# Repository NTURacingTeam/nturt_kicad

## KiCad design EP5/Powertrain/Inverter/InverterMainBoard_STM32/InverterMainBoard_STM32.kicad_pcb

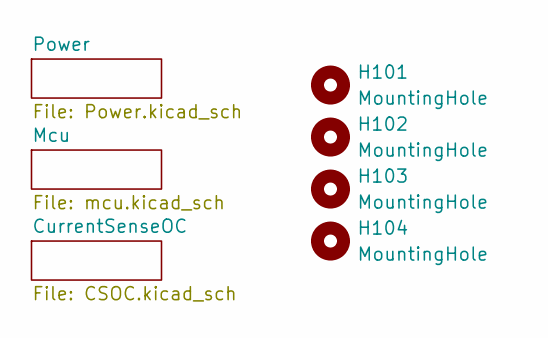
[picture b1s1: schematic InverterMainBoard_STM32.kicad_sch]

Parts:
H101, H102, H103, H104: MountingHole; MountingHole_4mm

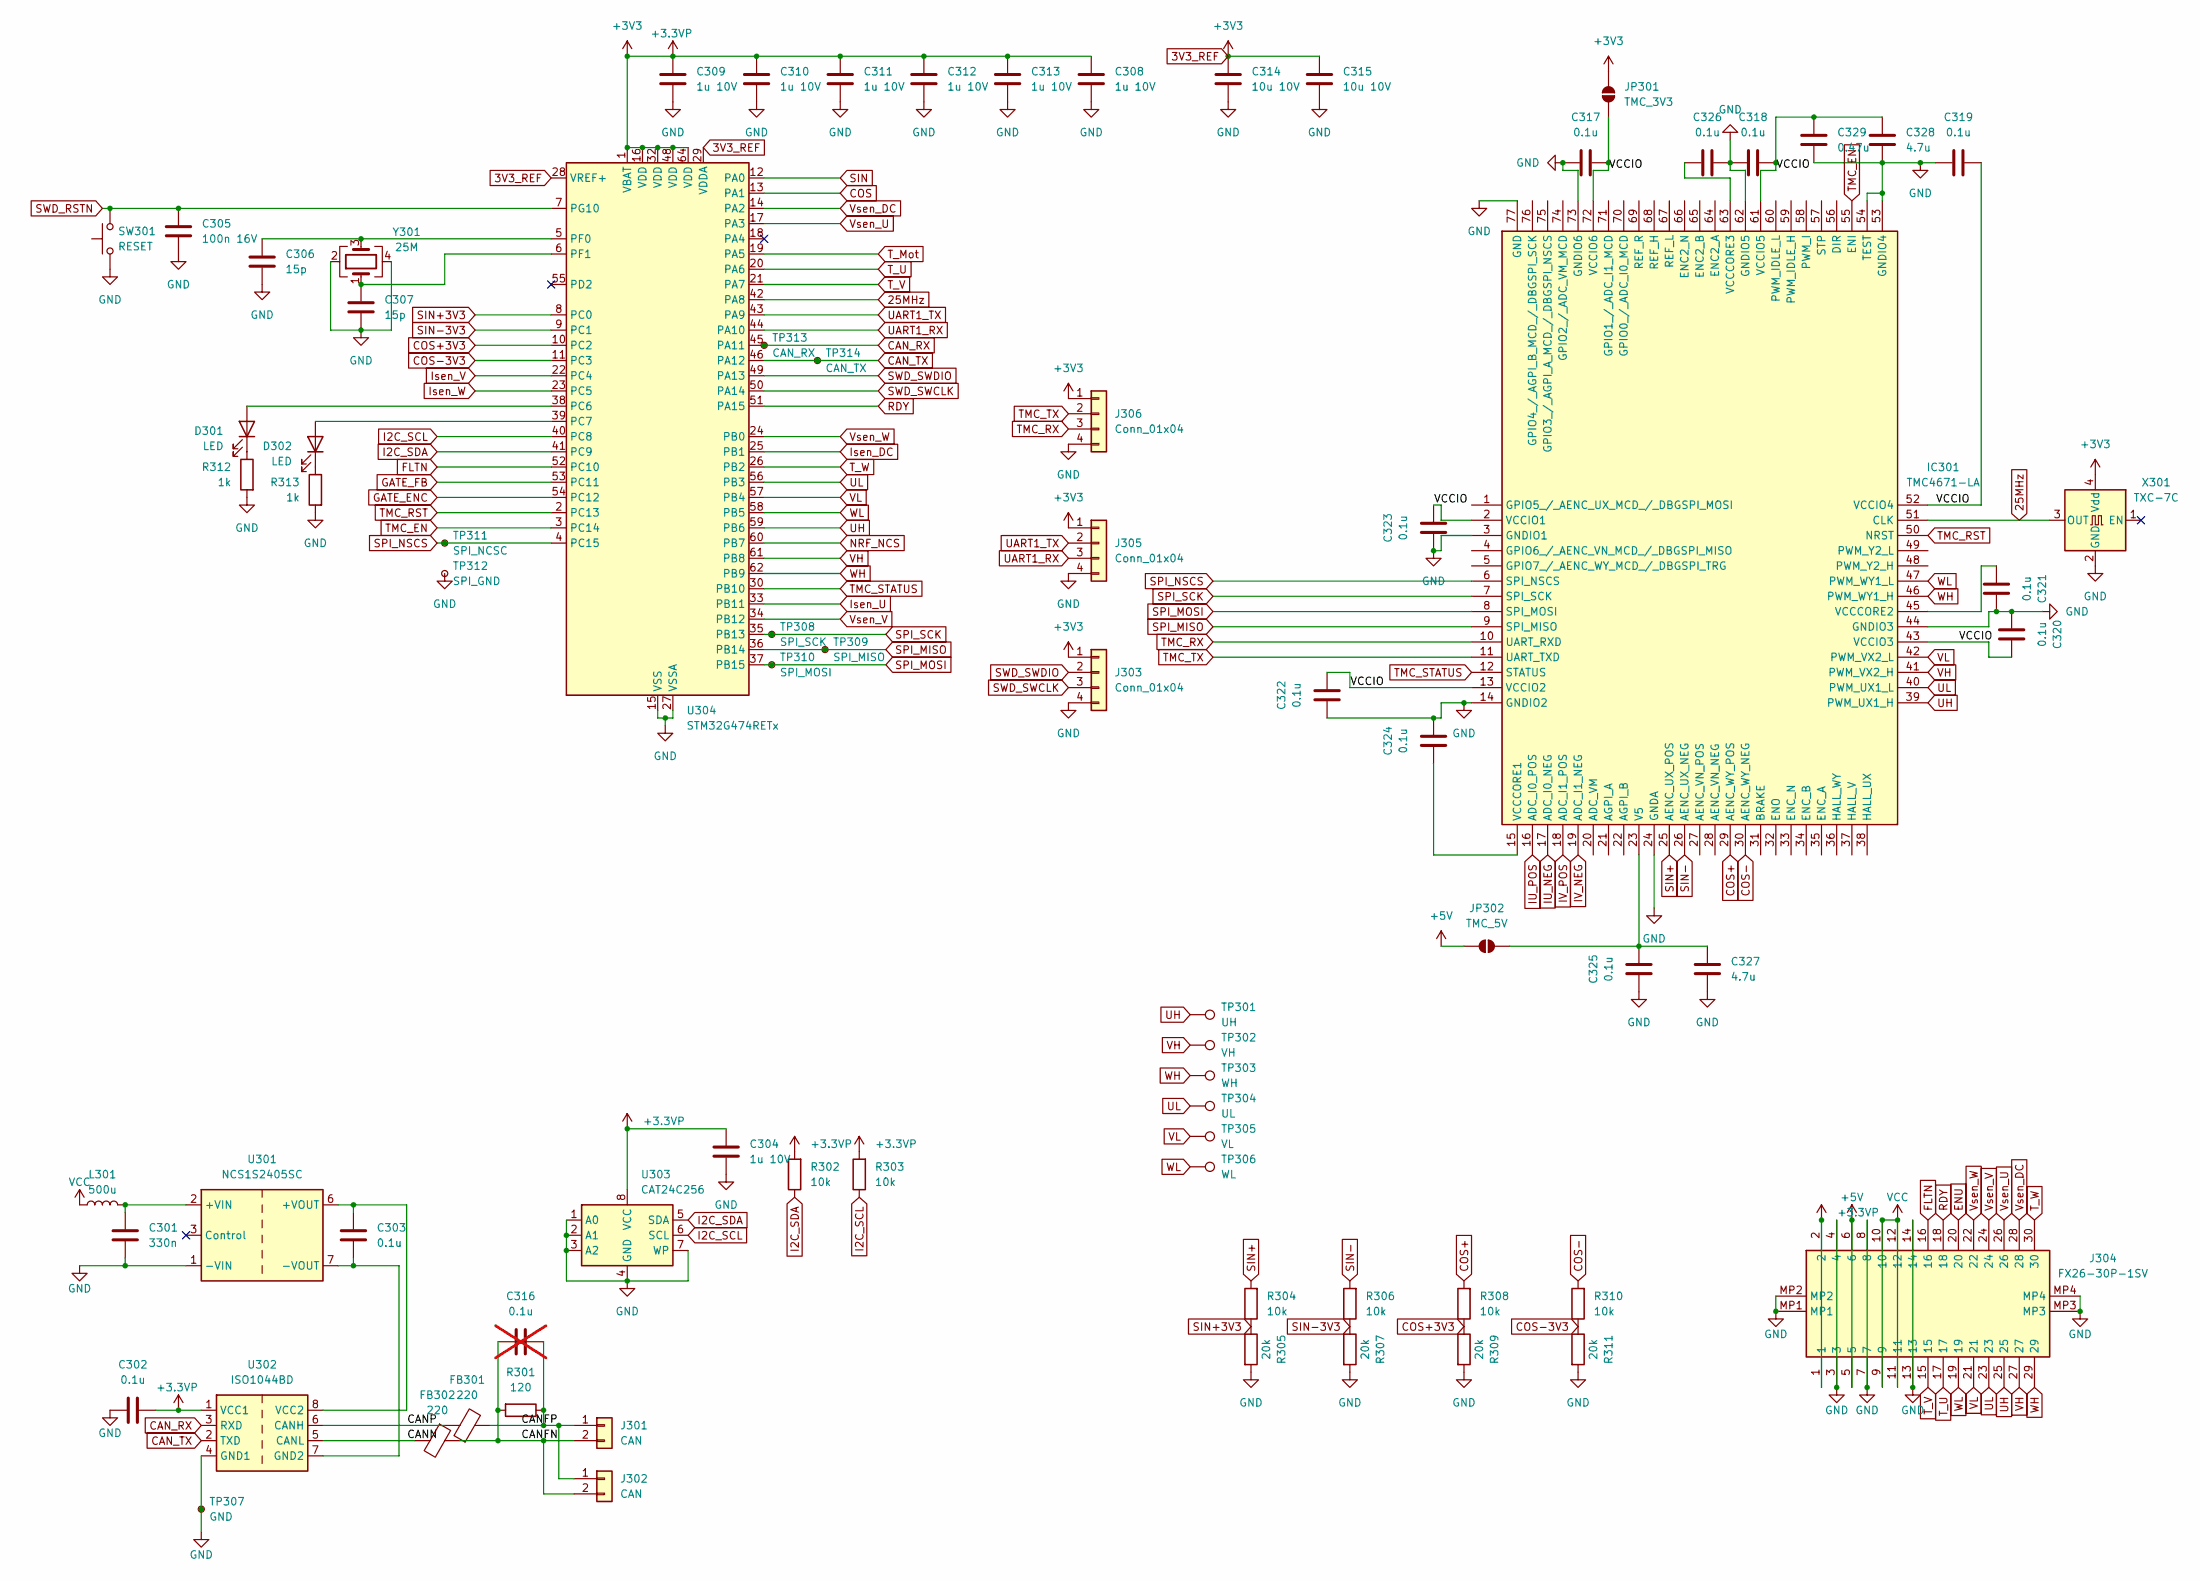
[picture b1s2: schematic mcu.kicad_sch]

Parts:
C301: 330n; C_0603_1608Metric
C302, C303, C317, C318, C319, C320, C321, C322, C323, C324, C325, C326: 0.1u; C_0603_1608Metric
C304, C308, C309, C310, C311, C312, C313: 1u 10V; C_0603_1608Metric
C305: 100n 16V; C_0603_1608Metric
C306, C307: 15p; C_0603_1608Metric
C314, C315: 10u 10V; C_0603_1608Metric
C316: 0.1u; C_0603_1608Metric; not fitted
C327, C328: 4.7u; C_0603_1608Metric
C329: 0.47u; C_0603_1608Metric
D301, D302: LED; LED_0603_1608Metric
FB301, FB302: 220; R_0603_1608Metric
IC301: TMC4671-LA; QFN40P1050X650X90-77N; Mouser Part Number 700-TMC4671-LA
J301, J302: CAN; JST_XH_B2B-XH-A_1x02_P2.50mm_Vertical
J303, J305, J306: Conn_01x04; PinHeader_1x04_P2.54mm_Vertical
J304: FX26-30P-1SV; FX2630P1SV; Mouser Part Number 798-FX2630P1SV
JP301: TMC_3V3; SolderJumper-2_P1.3mm_Open_Pad1.0x1.5mm
JP302: TMC_5V; SolderJumper-2_P1.3mm_Open_Pad1.0x1.5mm
L301: 500u; L_Changjiang_FNR4030S
R301: 120; R_0603_1608Metric
R302, R303, R304, R306, R308, R310: 10k; R_0603_1608Metric
R305, R307, R309, R311: 20k; R_0603_1608Metric
R312, R313: 1k; R_0603_1608Metric
SW301: RESET; SW_Push_1P1T_XKB_TS-1187A
TP301: UH; TestPoint_Pad_D1.0mm
TP302: VH; TestPoint_Pad_D1.0mm
TP303: WH; TestPoint_Pad_D1.0mm
TP304: UL; TestPoint_Pad_D1.0mm
TP305: VL; TestPoint_Pad_D1.0mm
TP306: WL; TestPoint_Pad_D1.0mm
TP307: GND; TestPoint_Loop_D1.80mm_Drill1.0mm_Beaded
TP308: SPI_SCK; TestPoint_Pad_D1.0mm
TP309: SPI_MISO; TestPoint_Pad_D1.0mm
TP310: SPI_MOSI; TestPoint_Pad_D1.0mm
TP311: SPI_NCSC; TestPoint_Pad_D1.0mm
TP312: SPI_GND; TestPoint_Pad_D1.0mm
TP313: CAN_RX; TestPoint_Pad_D1.0mm
TP314: CAN_TX; TestPoint_Pad_D1.0mm
U301: NCS1S2405SC; Converter_DCDC_Murata_NCS1SxxxxSC_THT
U302: ISO1044BD; SOIC-8_3.9x4.9mm_P1.27mm
U303: CAT24C256; SOIC-8_3.9x4.9mm_P1.27mm
U304: STM32G474RETx; LQFP-64_10x10mm_P0.5mm
X301: TXC-7C; Oscillator_SMD_TXC_7C-4Pin_5.0x3.2mm
Y301: 25M; Crystal_SMD_3225-4Pin_3.2x2.5mm

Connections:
3V3_REF: C302.2, C304.1, C308.1, C309.1, C310.1, C311.1, C312.1, C313.1, C314.1, C315.1, J303.1, J304.1, J304.2, J305.1, J306.1, JP301.2 (B), R302.2, R303.2, U302.1 (VCC1), U303.8 (VCC), U304.1 (VBAT), U304.16 (VDD), U304.28 (VREF+), U304.29 (VDDA), U304.32 (VDD), U304.48 (VDD), U304.64 (VDD), X301.4 (Vdd); also elsewhere on the board
25MHz: IC301.51 (CLK), U304.42 (PA8), X301.3 (OUT)
+5V: J304.5, J304.6, JP302.2 (B); also elsewhere on the board
/Mcu/CANFN: C316.1, FB302.1, J301.2, J302.2, R301.2
/Mcu/CANFP: C316.2, FB301.2, J301.1, J302.1, R301.1
/Mcu/CANN: FB302.2, U302.5 (CANL)
/Mcu/CANP: FB301.1, U302.6 (CANH)
/Mcu/VCCIO: C317.2, C318.2, C319.2, C320.2, C322.2, C323.2, C328.2, C329.2, IC301.2 (VCCIO1), IC301.13 (VCCIO2), IC301.43 (VCCIO3), IC301.52 (VCCIO4), IC301.61 (VCCIO5), IC301.72 (VCCIO6), JP301.1 (A)
CAN_RX: TP313.1, U302.3 (RXD), U304.45 (PA11)
CAN_TX: TP314.1, U302.2 (TXD), U304.46 (PA12)
COS: U304.13 (PA1); also elsewhere on the board
COS+: IC301.29 (AENC_WY_POS), R308.2; also elsewhere on the board
COS+3V3: R308.1, R309.1, U304.10 (PC2)
COS-: IC301.30 (AENC_WY_NEG), R310.2; also elsewhere on the board
COS-3V3: R310.1, R311.1, U304.11 (PC3)
ENU: J304.20, U304.53 (PC11); also elsewhere on the board
FLTN: J304.16, U304.52 (PC10)
GATE_ENC: U304.54 (PC12); also elsewhere on the board
GND: C301.2, C302.1, C304.2, C305.1, C306.1, C307.1, C308.2, C309.2, C310.2, C311.2, C312.2, C313.2, C314.2, C315.2, C317.1, C318.1, C319.1, C320.1, C321.2, C322.1, C323.1, C324.2, C325.1, C326.2, C327.1, C328.1, C329.1, IC301.3 (GNDIO1), IC301.14 (GNDIO2), IC301.24 (GNDA), IC301.44 (GNDIO3), IC301.53 (GNDIO4), IC301.54 (TEST), IC301.62 (GNDIO5), IC301.73 (GNDIO6), IC301.77 (GND), J303.4, J304.3, J304.4, J304.7, J304.8, J304.13, J304.14, J304.MP1, J304.MP2, J304.MP3, J304.MP4, J305.4, J306.4, R305.2, R307.2, R309.2, R311.2, R312.2, R313.2, SW301.1, TP307.1, TP312.1, U301.1 (-VIN), U302.4 (GND1), U303.1 (A0), U303.2 (A1), U303.3 (A2), U303.4 (GND), U303.7 (WP), U304.15 (VSS), U304.27 (VSSA), U304.31 (VSS), U304.47 (VSS), U304.63 (VSS), X301.2 (GND), Y301.2, Y301.4; also elsewhere on the board
I2C_SCL: R303.1, U303.6 (SCL), U304.40 (PC8)
I2C_SDA: R302.1, U303.5 (SDA), U304.41 (PC9)
IU_NEG: IC301.17 (ADC_I0_NEG); also elsewhere on the board
IU_POS: IC301.16 (ADC_I0_POS); also elsewhere on the board
IV_NEG: IC301.19 (ADC_I1_NEG); also elsewhere on the board
IV_POS: IC301.18 (ADC_I1_POS); also elsewhere on the board
Isen_DC: U304.25 (PB1); also elsewhere on the board
Isen_U: U304.33 (PB11); also elsewhere on the board
Isen_V: U304.22 (PC4); also elsewhere on the board
Isen_W: U304.23 (PC5); also elsewhere on the board
NRF_NCS: U304.60 (PB7)
unnamed: D301.2 (A), U304.38 (PC6)
unnamed: D301.1 (K), R312.1
unnamed: D302.2 (A), U304.39 (PC7)
unnamed: D302.1 (K), R313.1
unnamed: C325.2, C327.2, IC301.23 (V5), JP302.1 (A)
unnamed: C324.1, IC301.15 (VCCCORE1)
unnamed: C321.1, IC301.45 (VCCCORE2)
unnamed: C326.1, IC301.63 (VCCCORE3)
unnamed: C301.1, L301.2, U301.2 (+VIN)
unnamed: C303.1, U301.6 (+VOUT), U302.8 (VCC2)
unnamed: C303.2, U301.7 (-VOUT), U302.7 (GND2)
unnamed: C306.2, U304.5 (PF0), Y301.3
unnamed: C307.2, U304.6 (PF1), Y301.1
RDY: J304.18, U304.51 (PA15)
SIN: U304.12 (PA0); also elsewhere on the board
SIN+: IC301.25 (AENC_UX_POS), R304.2; also elsewhere on the board
SIN+3V3: R304.1, R305.1, U304.8 (PC0)
SIN-: IC301.26 (AENC_UX_NEG), R306.2; also elsewhere on the board
SIN-3V3: R306.1, R307.1, U304.9 (PC1)
SPI_MISO: IC301.9 (SPI_MISO), TP309.1, U304.36 (PB14)
SPI_MOSI: IC301.8 (SPI_MOSI), TP310.1, U304.37 (PB15)
SPI_NSCS: IC301.6 (SPI_NSCS), TP311.1, U304.4 (PC15)
SPI_SCK: IC301.7 (SPI_SCK), TP308.1, U304.35 (PB13)
SWD_RSTN: C305.2, SW301.2, U304.7 (PG10)
SWD_SWCLK: J303.3, U304.50 (PA14)
SWD_SWDIO: J303.2, U304.49 (PA13)
TMC_EN: IC301.55 (ENI), U304.3 (PC14)
TMC_RST: IC301.50 (NRST), U304.2 (PC13)
TMC_RX: IC301.10 (UART_RXD), J306.3
TMC_STATUS: IC301.12 (STATUS), U304.30 (PB10)
TMC_TX: IC301.11 (UART_TXD), J306.2
T_Mot: U304.19 (PA5); also elsewhere on the board
T_U: J304.17, U304.20 (PA6)
T_V: J304.15, U304.21 (PA7)
T_W: J304.30, U304.26 (PB2)
UART1_RX: J305.3, U304.44 (PA10)
UART1_TX: J305.2, U304.43 (PA9)
UH: IC301.39 (PWM_UX1_H), J304.25, TP301.1, U304.59 (PB6)
UL: IC301.40 (PWM_UX1_L), J304.23, TP304.1, U304.56 (PB3)
VCC: J304.9, J304.10, J304.11, J304.12, L301.1; also elsewhere on the board
VH: IC301.41 (PWM_VX2_H), J304.27, TP302.1, U304.61 (PB8)
VL: IC301.42 (PWM_VX2_L), J304.21, TP305.1, U304.57 (PB4)
Vsen_DC: J304.28, U304.14 (PA2)
Vsen_U: J304.26, U304.17 (PA3)
Vsen_V: J304.24, U304.34 (PB12)
Vsen_W: J304.22, U304.24 (PB0)
WH: IC301.46 (PWM_WY1_H), J304.29, TP303.1, U304.62 (PB9)
WL: IC301.47 (PWM_WY1_L), J304.19, TP306.1, U304.58 (PB5)

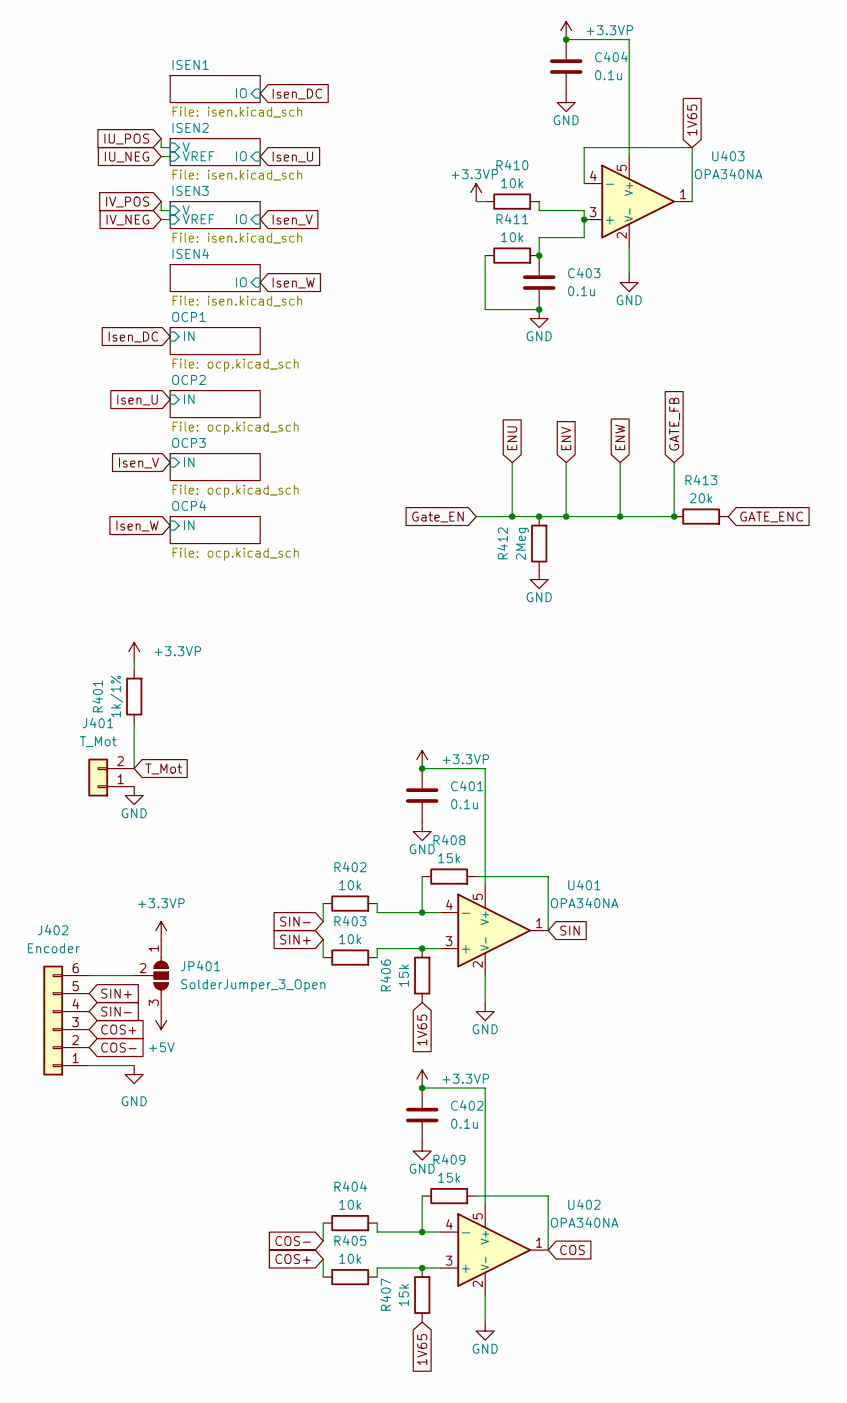
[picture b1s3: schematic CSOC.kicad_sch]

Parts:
C401, C402, C403, C404: 0.1u; C_0603_1608Metric
J401: T_Mot; JST_XH_B2B-XH-A_1x02_P2.50mm_Vertical
J402: Encoder; JST_XH_B6B-XH-A_1x06_P2.50mm_Vertical
JP401: SolderJumper_3_Open; SolderJumper-3_P1.3mm_Open_Pad1.0x1.5mm
R401: 1k/1%; R_0603_1608Metric
R402, R403, R404, R405, R410, R411: 10k; R_0603_1608Metric
R406, R407, R408, R409: 15k; R_0603_1608Metric
R412: 2Meg; R_0603_1608Metric
R413: 20k; R_0603_1608Metric
U401, U402, U403: OPA340NA; SOT-23-5

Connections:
1V65: R406.1, R407.1, U403.1, U403.4 (-); also elsewhere on the board
3V3_REF: C401.2, C402.2, C404.2, JP401.1 (A), R401.2, R410.1, U401.5 (V+), U402.5 (V+), U403.5 (V+); also elsewhere on the board
+5V: JP401.3 (B); also elsewhere on the board
COS: R409.2, U402.1; also elsewhere on the board
COS+: J402.3, R405.1; also elsewhere on the board
COS-: J402.2, R404.1; also elsewhere on the board
ENU: R412.2, R413.1; also elsewhere on the board
GATE_ENC: R413.2; also elsewhere on the board
GND: C401.1, C402.1, C403.1, C404.1, J401.1, J402.1, R411.1, R412.1, U401.2 (V-), U402.2 (V-), U403.2 (V-); also elsewhere on the board
unnamed: J402.6, JP401.2 (C)
unnamed: R403.2, R406.2, U401.3 (+)
unnamed: R402.2, R408.1, U401.4 (-)
unnamed: R405.2, R407.2, U402.3 (+)
unnamed: R404.2, R409.1, U402.4 (-)
unnamed: C403.2, R410.2, R411.2, U403.3 (+)
SIN: R408.2, U401.1; also elsewhere on the board
SIN+: J402.5, R403.1; also elsewhere on the board
SIN-: J402.4, R402.1; also elsewhere on the board
T_Mot: J401.2, R401.1; also elsewhere on the board

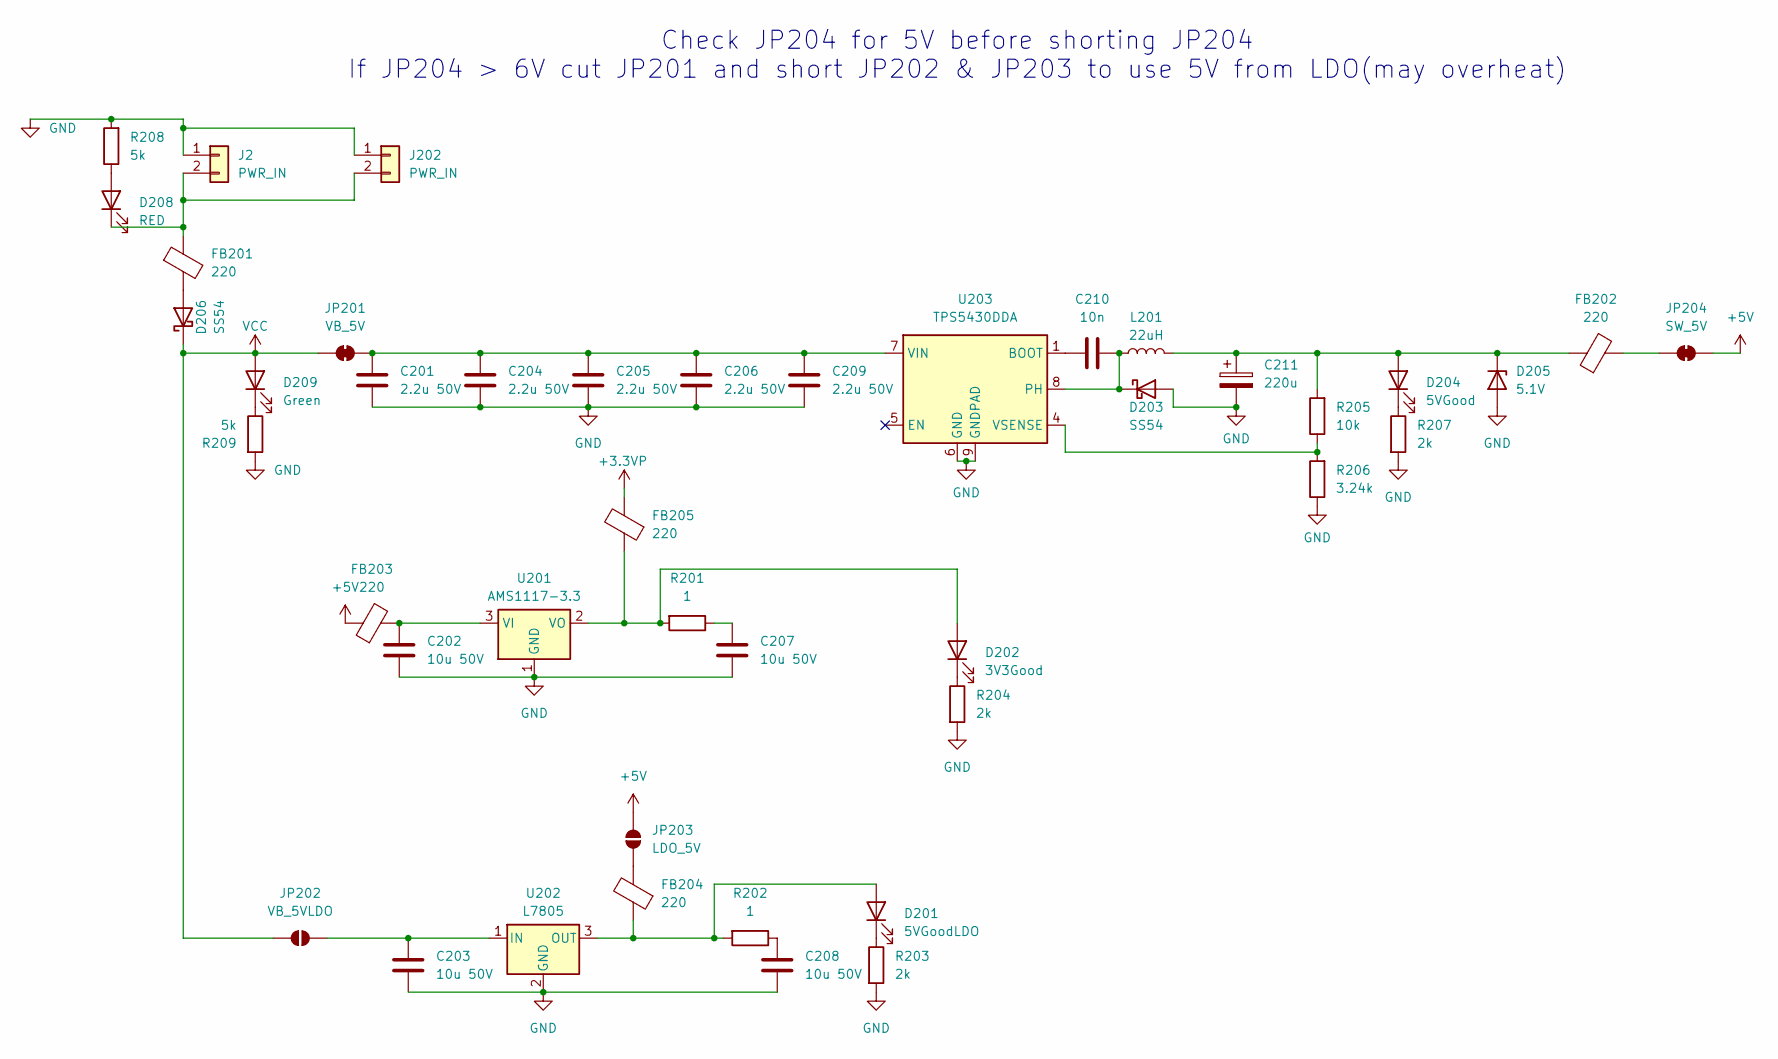
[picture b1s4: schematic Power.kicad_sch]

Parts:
C201, C204, C205, C206, C209: 2.2u 50V; C_0805_2012Metric
C202, C203, C207, C208: 10u 50V; C_1206_3216Metric
C210: 10n; C_0603_1608Metric
C211: 220u; CP_Elec_8x10.5
D201: 5VGoodLDO; LED_0603_1608Metric
D202: 3V3Good; LED_0603_1608Metric
D203, D206: SS54; D_SMA
D204: 5VGood; LED_0603_1608Metric
D205: 5.1V; D_SOD-123
D208: RED; LED_0603_1608Metric
D209: Green; LED_0603_1608Metric
FB201, FB202, FB203, FB204, FB205: 220; R_0603_1608Metric
J2, J202: PWR_IN; JST_XH_B2B-XH-A_1x02_P2.50mm_Vertical
JP201: VB_5V; SolderJumper-2_P1.3mm_Bridged_Pad1.0x1.5mm
JP202: VB_5VLDO; SolderJumper-2_P1.3mm_Open_Pad1.0x1.5mm
JP203: LDO_5V; SolderJumper-2_P1.3mm_Open_Pad1.0x1.5mm
JP204: SW_5V; SolderJumper-2_P1.3mm_Open_Pad1.0x1.5mm
L201: 22uH; L_Bourns_SRR1260
R201, R202: 1; R_1206_3216Metric
R203, R204, R207: 2k; R_0603_1608Metric
R205: 10k; R_0603_1608Metric
R206: 3.24k; R_0603_1608Metric
R208, R209: 5k; R_0603_1608Metric
U201: AMS1117-3.3; SOT-223-3_TabPin2
U202: L7805; TO-252-2
U203: TPS5430DDA; TI_SO-PowerPAD-8_ThermalVias

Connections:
3V3_REF: FB205.2; also elsewhere on the board
+5V: FB203.1, JP203.2 (B), JP204.2 (B); also elsewhere on the board
GND: C201.2, C202.2, C203.2, C204.2, C205.2, C206.2, C207.2, C208.2, C209.2, C211.2, D203.2 (A), D205.2 (A), J202.1, R203.2, R204.2, R206.1, R207.2, R208.2, R209.2, U201.1 (GND), U202.2 (GND), U203.6 (GND), U203.9 (GNDPAD); also elsewhere on the board
unnamed: C207.1, R201.1
unnamed: C208.1, R202.1
unnamed: D201.2 (A), FB204.1, R202.2, U202.3 (OUT)
unnamed: D201.1 (K), R203.1
unnamed: D202.2 (A), FB205.1, R201.2, U201.2 (VO)
unnamed: D202.1 (K), R204.1
unnamed: C210.2, D203.1 (K), L201.1, U203.8 (PH)
unnamed: C211.1, D204.2 (A), D205.1 (K), FB202.1, L201.2, R205.2
unnamed: D204.1 (K), R207.1
unnamed: D206.2 (A), FB201.2
unnamed: D208.2 (A), R208.1
unnamed 46: D208.1 (K), FB201.1, J202.2; also elsewhere on the board
unnamed: D209.1 (K), R209.1
unnamed: C201.1, C204.1, C205.1, C206.1, C209.1, JP201.2 (B), U203.7 (VIN)
unnamed: C203.1, JP202.2 (B), U202.1 (IN)
unnamed: FB204.2, JP203.1 (A)
unnamed: FB202.2, JP204.1 (A)
unnamed: C202.1, FB203.2, U201.3 (VI)
unnamed: C210.1, U203.1 (BOOT)
unnamed: R205.1, R206.2, U203.4 (VSENSE)
VCC: D206.1 (K), D209.2 (A), JP201.1 (A), JP202.1 (A); also elsewhere on the board

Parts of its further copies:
J201: PWR_IN; JST_XH_B2B-XH-A_1x02_P2.50mm_Vertical

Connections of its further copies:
GND: J201.1; also elsewhere on the board
unnamed 46: J201.2; also elsewhere on the board

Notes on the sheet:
Check JP204 for 5V before shorting JP204 If JP204 > 6V cut JP201 and short JP202 & JP203 to use 5V from LDO(may overheat)

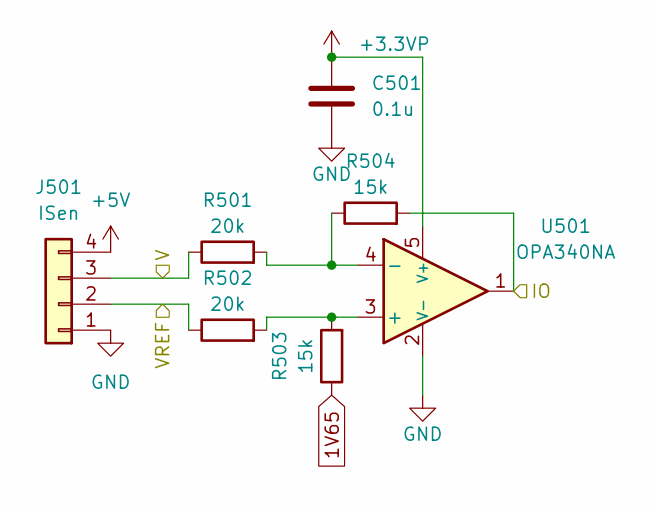
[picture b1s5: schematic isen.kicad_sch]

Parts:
C501: 0.1u; C_0603_1608Metric
J501: ISen; JST_XH_B4B-XH-A_1x04_P2.50mm_Vertical
R501, R502: 20k; R_0603_1608Metric
R503, R504: 15k; R_0603_1608Metric
U501: OPA340NA; SOT-23-5

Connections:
1V65: R503.1; also elsewhere on the board
3V3_REF: C501.2, U501.5 (V+); also elsewhere on the board
+5V: J501.4; also elsewhere on the board
/CurrentSenseOC/ISEN1/V: J501.3, R501.1
/CurrentSenseOC/ISEN1/VREF: J501.2, R502.1
GND: C501.1, J501.1, U501.2 (V-); also elsewhere on the board
Isen_DC: R504.2, U501.1; also elsewhere on the board
unnamed: R502.2, R503.2, U501.3 (+)
unnamed: R501.2, R504.1, U501.4 (-)

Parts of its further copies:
C601, C701, C801: 0.1u; C_0603_1608Metric
J601, J701, J801: ISen; JST_XH_B4B-XH-A_1x04_P2.50mm_Vertical
R601, R602, R701, R702, R801, R802: 20k; R_0603_1608Metric
R603, R604, R703, R704, R803, R804: 15k; R_0603_1608Metric
U601, U701, U801: OPA340NA; SOT-23-5

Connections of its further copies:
1V65: R603.1, R703.1, R803.1; also elsewhere on the board
3V3_REF: C601.2, C701.2, C801.2, U601.5 (V+), U701.5 (V+), U801.5 (V+); also elsewhere on the board
+5V: J601.4, J701.4, J801.4; also elsewhere on the board
/CurrentSenseOC/ISEN4/V: J801.3, R801.1
/CurrentSenseOC/ISEN4/VREF: J801.2, R802.1
GND: C601.1, C701.1, C801.1, J601.1, J701.1, J801.1, U601.2 (V-), U701.2 (V-), U801.2 (V-); also elsewhere on the board
IU_NEG: J601.2, R602.1; also elsewhere on the board
IU_POS: J601.3, R601.1; also elsewhere on the board
IV_NEG: J701.2, R702.1; also elsewhere on the board
IV_POS: J701.3, R701.1; also elsewhere on the board
Isen_U: R604.2, U601.1; also elsewhere on the board
Isen_V: R704.2, U701.1; also elsewhere on the board
Isen_W: R804.2, U801.1; also elsewhere on the board
unnamed: R602.2, R603.2, U601.3 (+)
unnamed: R601.2, R604.1, U601.4 (-)
unnamed: R702.2, R703.2, U701.3 (+)
unnamed: R701.2, R704.1, U701.4 (-)
unnamed: R802.2, R803.2, U801.3 (+)
unnamed: R801.2, R804.1, U801.4 (-)

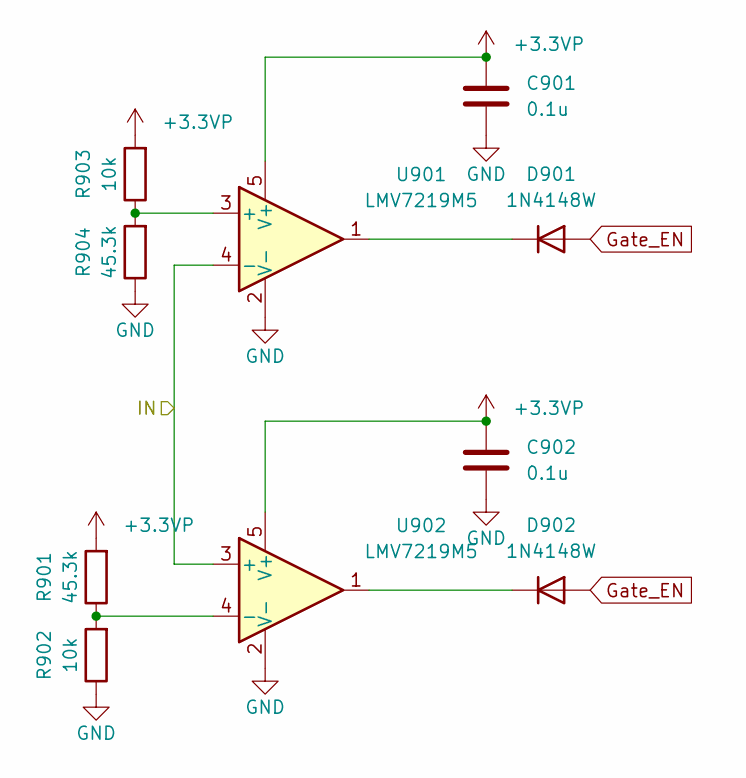
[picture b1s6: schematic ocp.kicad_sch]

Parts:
C901, C902: 0.1u; C_0603_1608Metric
D901, D902: 1N4148W; D_SOD-123
R901, R904: 45.3k; R_0603_1608Metric
R902, R903: 10k; R_0603_1608Metric
U901, U902: LMV7219M5; SOT-23-5

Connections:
3V3_REF: C901.2, C902.2, R901.2, R903.2, U901.5 (V+), U902.5 (V+); also elsewhere on the board
ENU: D901.2 (A), D902.2 (A); also elsewhere on the board
GND: C901.1, C902.1, R902.1, R904.1, U901.2 (V-), U902.2 (V-); also elsewhere on the board
Isen_DC: U901.4 (-), U902.3 (+); also elsewhere on the board
unnamed: D901.1 (K), U901.1
unnamed: D902.1 (K), U902.1
unnamed: R903.1, R904.2, U901.3 (+)
unnamed: R901.1, R902.2, U902.4 (-)

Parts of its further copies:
C1001, C1002, C1101, C1102, C1201, C1202: 0.1u; C_0603_1608Metric
D1001, D1002, D1101, D1102, D1201, D1202: 1N4148W; D_SOD-123
R1001, R1004, R1101, R1104, R1201, R1204: 45.3k; R_0603_1608Metric
R1002, R1003, R1102, R1103, R1202, R1203: 10k; R_0603_1608Metric
U1001, U1002, U1101, U1102, U1201, U1202: LMV7219M5; SOT-23-5

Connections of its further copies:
3V3_REF: C1001.2, C1002.2, C1101.2, C1102.2, C1201.2, C1202.2, R1001.2, R1003.2, R1101.2, R1103.2, R1201.2, R1203.2, U1001.5 (V+), U1002.5 (V+), U1101.5 (V+), U1102.5 (V+), U1201.5 (V+), U1202.5 (V+); also elsewhere on the board
ENU: D1001.2 (A), D1002.2 (A), D1101.2 (A), D1102.2 (A), D1201.2 (A), D1202.2 (A); also elsewhere on the board
GND: C1001.1, C1002.1, C1101.1, C1102.1, C1201.1, C1202.1, R1002.1, R1004.1, R1102.1, R1104.1, R1202.1, R1204.1, U1001.2 (V-), U1002.2 (V-), U1101.2 (V-), U1102.2 (V-), U1201.2 (V-), U1202.2 (V-); also elsewhere on the board
Isen_U: U1001.4 (-), U1002.3 (+); also elsewhere on the board
Isen_V: U1101.4 (-), U1102.3 (+); also elsewhere on the board
Isen_W: U1201.4 (-), U1202.3 (+); also elsewhere on the board
unnamed: D1001.1 (K), U1001.1
unnamed: D1002.1 (K), U1002.1
unnamed: D1101.1 (K), U1101.1
unnamed: D1102.1 (K), U1102.1
unnamed: D1201.1 (K), U1201.1
unnamed: D1202.1 (K), U1202.1
unnamed: R1003.1, R1004.2, U1001.3 (+)
unnamed: R1001.1, R1002.2, U1002.4 (-)
unnamed: R1103.1, R1104.2, U1101.3 (+)
unnamed: R1101.1, R1102.2, U1102.4 (-)
unnamed: R1203.1, R1204.2, U1201.3 (+)
unnamed: R1201.1, R1202.2, U1202.4 (-)

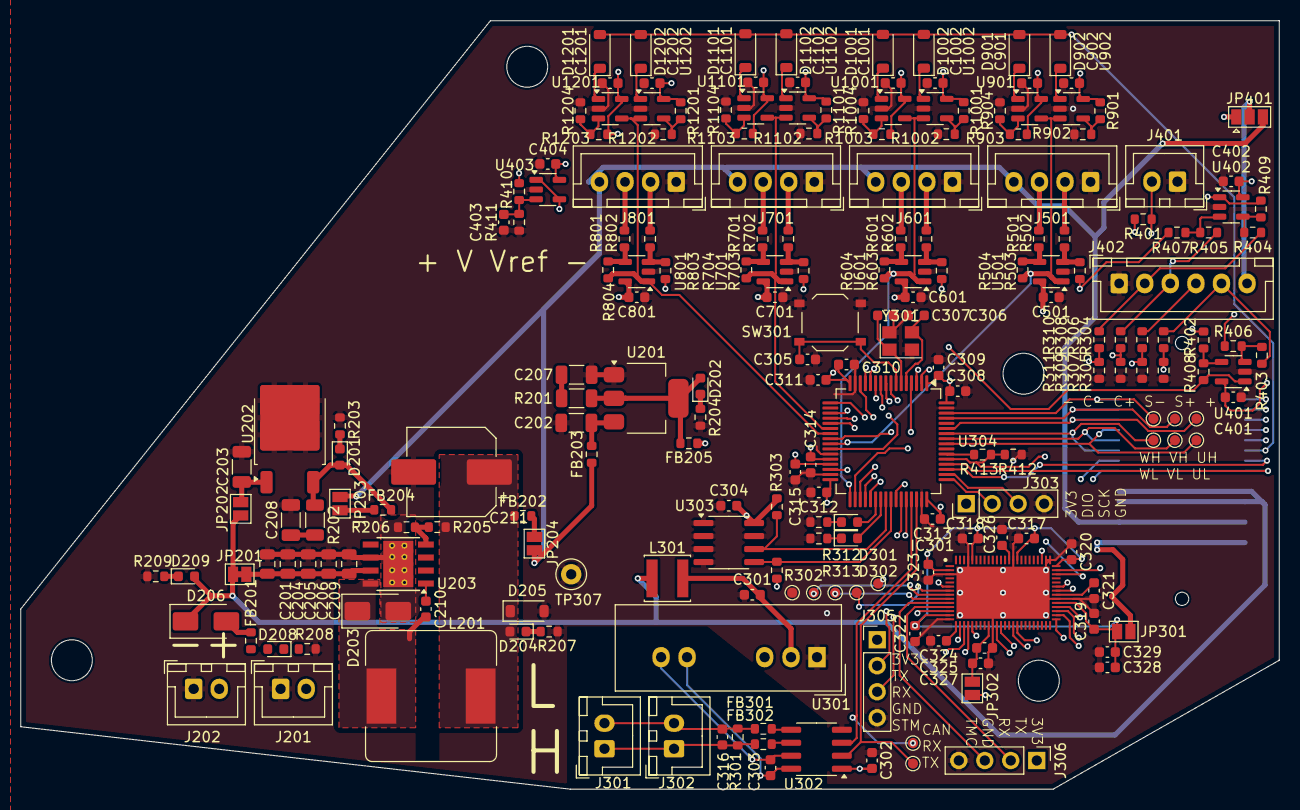
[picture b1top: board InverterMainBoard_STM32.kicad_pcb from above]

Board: 4 copper layers, 123.0 x 75.1 mm, 214 parts (1 on the bottom side), 132 nets.

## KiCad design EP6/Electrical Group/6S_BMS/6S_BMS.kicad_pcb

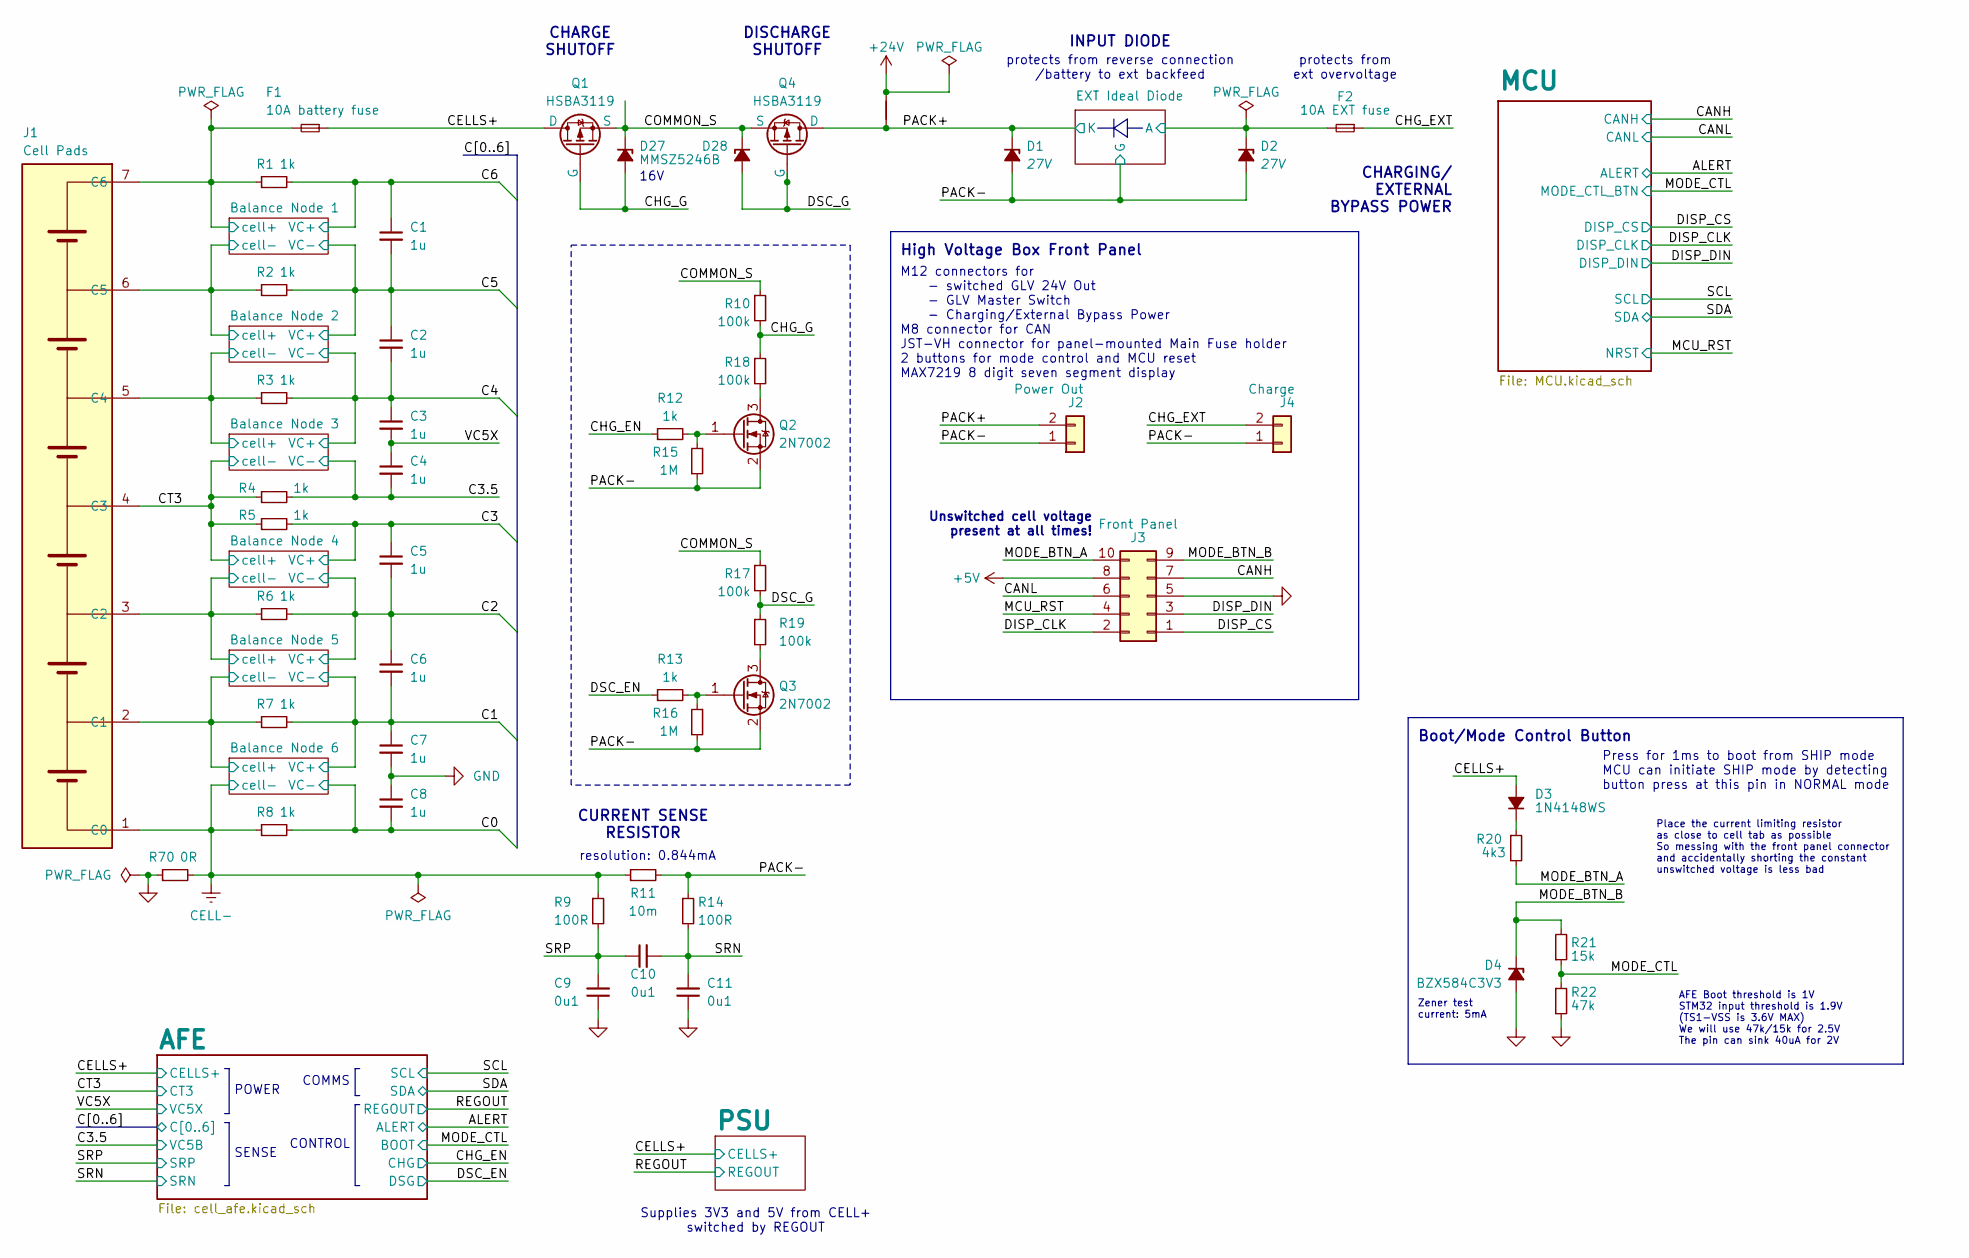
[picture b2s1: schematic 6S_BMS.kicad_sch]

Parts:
C1, C2, C3, C4, C5, C6, C7, C8: 1u; C_0402_1005Metric
C9, C10, C11: 0u1; C_0402_1005Metric
D1, D2: 27V; D_SOD-123
D3: 1N4148WS; D_SOD-323
D4: BZX584C3V3; D_SOD-323
D27, D28: MMSZ5246B; D_SOD-123
F1: 10A battery fuse; Fuse_1210_3225Metric_Pad1.42x2.65mm_HandSolder
F2: 10A EXT fuse; Fuse_1210_3225Metric_Pad1.42x2.65mm_HandSolder
J1: Cell Pads; 6S_batteries_100mm_across
J2: Power Out; AMASS_XT60PW-F_1x02_P7.20mm_Horizontal
J3: Front Panel; IDC-Header_2x05_P2.54mm_Horizontal
J4: Charge; AMASS_XT60PW-M_1x02_P7.20mm_Horizontal
NT2: NetTie_2
Q1, Q4: HSBA3119; HSBA3119_PRPAK5X6
Q2, Q3: 2N7002; SOT-23
R1, R2, R3, R4, R5, R6, R7, R8, R12, R13: 1k; R_0402_1005Metric
R9, R14: 100R; R_0402_1005Metric
R10, R17, R18, R19: 100k; R_0402_1005Metric
R11: 10m; R_2512_6332Metric
R15, R16: 1M; R_0402_1005Metric
R20: 4k3; R_0402_1005Metric
R21: 15k; R_0402_1005Metric
R22: 47k; R_0402_1005Metric
R70: 0R; R_0805_2012Metric_Pad1.20x1.40mm_HandSolder

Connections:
+5V: J3.8; also elsewhere on the board
/Balance Node 1/cell+: F1.2, J1.7 (C6), R1.1; also elsewhere on the board
/Balance Node 1/cell-: J1.6 (C5), R2.1; also elsewhere on the board
/Balance Node 4/cell-: J1.3 (C2), R6.1; also elsewhere on the board
/Balance Node 5/cell-: J1.2 (C1), R7.1; also elsewhere on the board
/C0: C8.2, R8.2; also elsewhere on the board
/C1: C6.2, C7.1, R7.2; also elsewhere on the board
/C2: C5.2, C6.1, R6.2; also elsewhere on the board
/C3: C5.1, R5.2; also elsewhere on the board
/C3.5: C4.2, R4.2; also elsewhere on the board
/C4: C2.2, C3.1, R3.2; also elsewhere on the board
/C5: C1.2, C2.1, R2.2; also elsewhere on the board
/CANH: J3.7; also elsewhere on the board
/CANL: J3.6; also elsewhere on the board
/CELLS+: D3.2 (A), F1.1, Q1.D; also elsewhere on the board
/CHG_EN: R12.1; also elsewhere on the board
/CHG_EXT: F2.1, J4.2
/CHG_G: D27.2 (A), Q1.G, R10.2, R18.1
/COMMON_S: D27.1 (K), D28.1 (K), Q1.S, Q4.S, R10.1, R17.1
/CT3: J1.4 (C3), R4.1, R5.1; also elsewhere on the board
/DISP_CLK: J3.2; also elsewhere on the board
/DISP_CS: J3.1; also elsewhere on the board
/DISP_DIN: J3.3; also elsewhere on the board
/DSC_EN: R13.1; also elsewhere on the board
/DSC_G: D28.2 (A), Q4.G, R17.2, R19.1
/EXT Ideal Diode/A: D2.1 (K), F2.2; also elsewhere on the board
/MCU_RST: J3.4; also elsewhere on the board
/MODE_BTN_A: J3.10, R20.2
/MODE_BTN_B: D4.1 (K), J3.9, R21.2
/MODE_CTL: R21.1, R22.1; also elsewhere on the board
/PACK+: D1.1 (K), J2.2, NT2.1, Q4.D; also elsewhere on the board
/PACK-: D1.2 (A), D2.2 (A), J2.1, J4.1, Q2.2 (S), Q3.2 (S), R11.2, R14.1, R15.2, R16.2; also elsewhere on the board
/SRN: C10.2, C11.2, R14.2; also elsewhere on the board
/SRP: C9.2, C10.1, R9.2; also elsewhere on the board
/VC5X: C3.2, C4.1; also elsewhere on the board
CELL-: J1.1 (C0), R8.1, R9.1, R11.1, R70.2; also elsewhere on the board
GND: C7.2, C8.1, C9.1, C11.1, D4.2 (A), J3.5, R22.2, R70.1; also elsewhere on the board
unnamed: D3.1 (K), R20.1
unnamed: Q2.3 (D), R18.2
unnamed: Q2.1 (G), R12.2, R15.1
unnamed: Q3.3 (D), R19.2
unnamed: Q3.1 (G), R13.2, R16.1

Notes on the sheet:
CHARGE SHUTOFF
DISCHARGE SHUTOFF
Unswitched cell voltage present at all times!
COMMS
Place the current limiting resistor as close to cell tab as possible So messing with the front panel connector and accidentally shorting the constant unswitched voltage is less bad
POWER
protects from ext overvoltage
protects from reverse connection /battery to ext backfeed
INPUT DIODE
Zener test current: 5mA
Supplies 3V3 and 5V from CELL+ switched by REGOUT
Boot/Mode Control Button
CHARGING/ EXTERNAL BYPASS POWER
AFE Boot threshold is 1V STM32 input threshold is 1.9V (TS1-VSS is 3.6V MAX) We will use 47k/15k for 2.5V The pin can sink 40uA for 2V
M12 connectors for - switched GLV 24V Out - GLV Master Switch - Charging/External Bypass Power M8 connector for CAN JST-VH connector for panel-mounted Main Fuse holder 2 buttons for mode control and MCU reset MAX7219 8 digit seven segment display
resolution: 0.844mA
CONTROL
High Voltage Box Front Panel
CURRENT SENSE RESISTOR
Press for 1ms to boot from SHIP mode MCU can initiate SHIP mode by detecting button press at this pin in NORMAL mode
SENSE
16V
